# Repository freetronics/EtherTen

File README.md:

Freetronics EtherTen
====================
Copyright 2010-2013 Freetronics Pty Ltd  
Freetronics site:  www.freetronics.com  
Freetronics email: info@freetronics.com  

The EtherTen is a 100% Arduino Compatible Board, based on the Arduino
Uno reference design, but with improvements and updates for ease of use, cost
and getting started. It also includes on-board Ethernet with PoE (Power
-over-Ethernet) support.

Features:

 * LEDs visible on the edge
 * Micro-USB Connector
 * I2C MAC address ROM
 * Overlay guide where you need it (both top and bottom)
 * D13 pin works for everything
 * RX pin biased
 * Mounting holes, power and X3 pads
 * All connections in the same place

You can view more at our product page at:

  http://www.freetronics.com/etherten

This repository includes a handy copy of the schematic in PDF format.

INSTALLATION
------------
The design is saved as an EAGLE project. EAGLE PCB design software is
available from www.cadsoftusa.com free for non-commercial use. To use
this project download it and place the directory containing these files
into the "eagle" directory on your computer. Then open EAGLE and
navigate to Projects -> eagle -> EtherTen.

DISTRIBUTION
------------
The specific terms of distribution of this project are governed by the
license referenced below.

LICENSE
-------
This work is licensed under the
Creative Commons Attribution-Share Alike License.  
To view a copy of this license, visit

  http://creativecommons.org/licenses/by-sa/3.0/  
  http://creativecommons.org/licenses/by-sa/3.0/legalcode

or send a letter to

  Creative Commons  
  171 Second Street, Suite 300  
  San Francisco  
  California, 94105  
  USA

The "license" folder within this repository also contains copies of the
licences referenced above.

CREDITS
-------
The EtherTen was designed by Marc Alexander (marc@freetronics.com) and
Jonathan Oxer (jon@freetronics.com) based on previous work by the Arduino
team (www.arduino.cc/playground/Main/People) which includes:

 * Massimo Banzi
 * David Cuartielles
 * Tom Igoe
 * Gianluca Martino
 * David A. Mellis

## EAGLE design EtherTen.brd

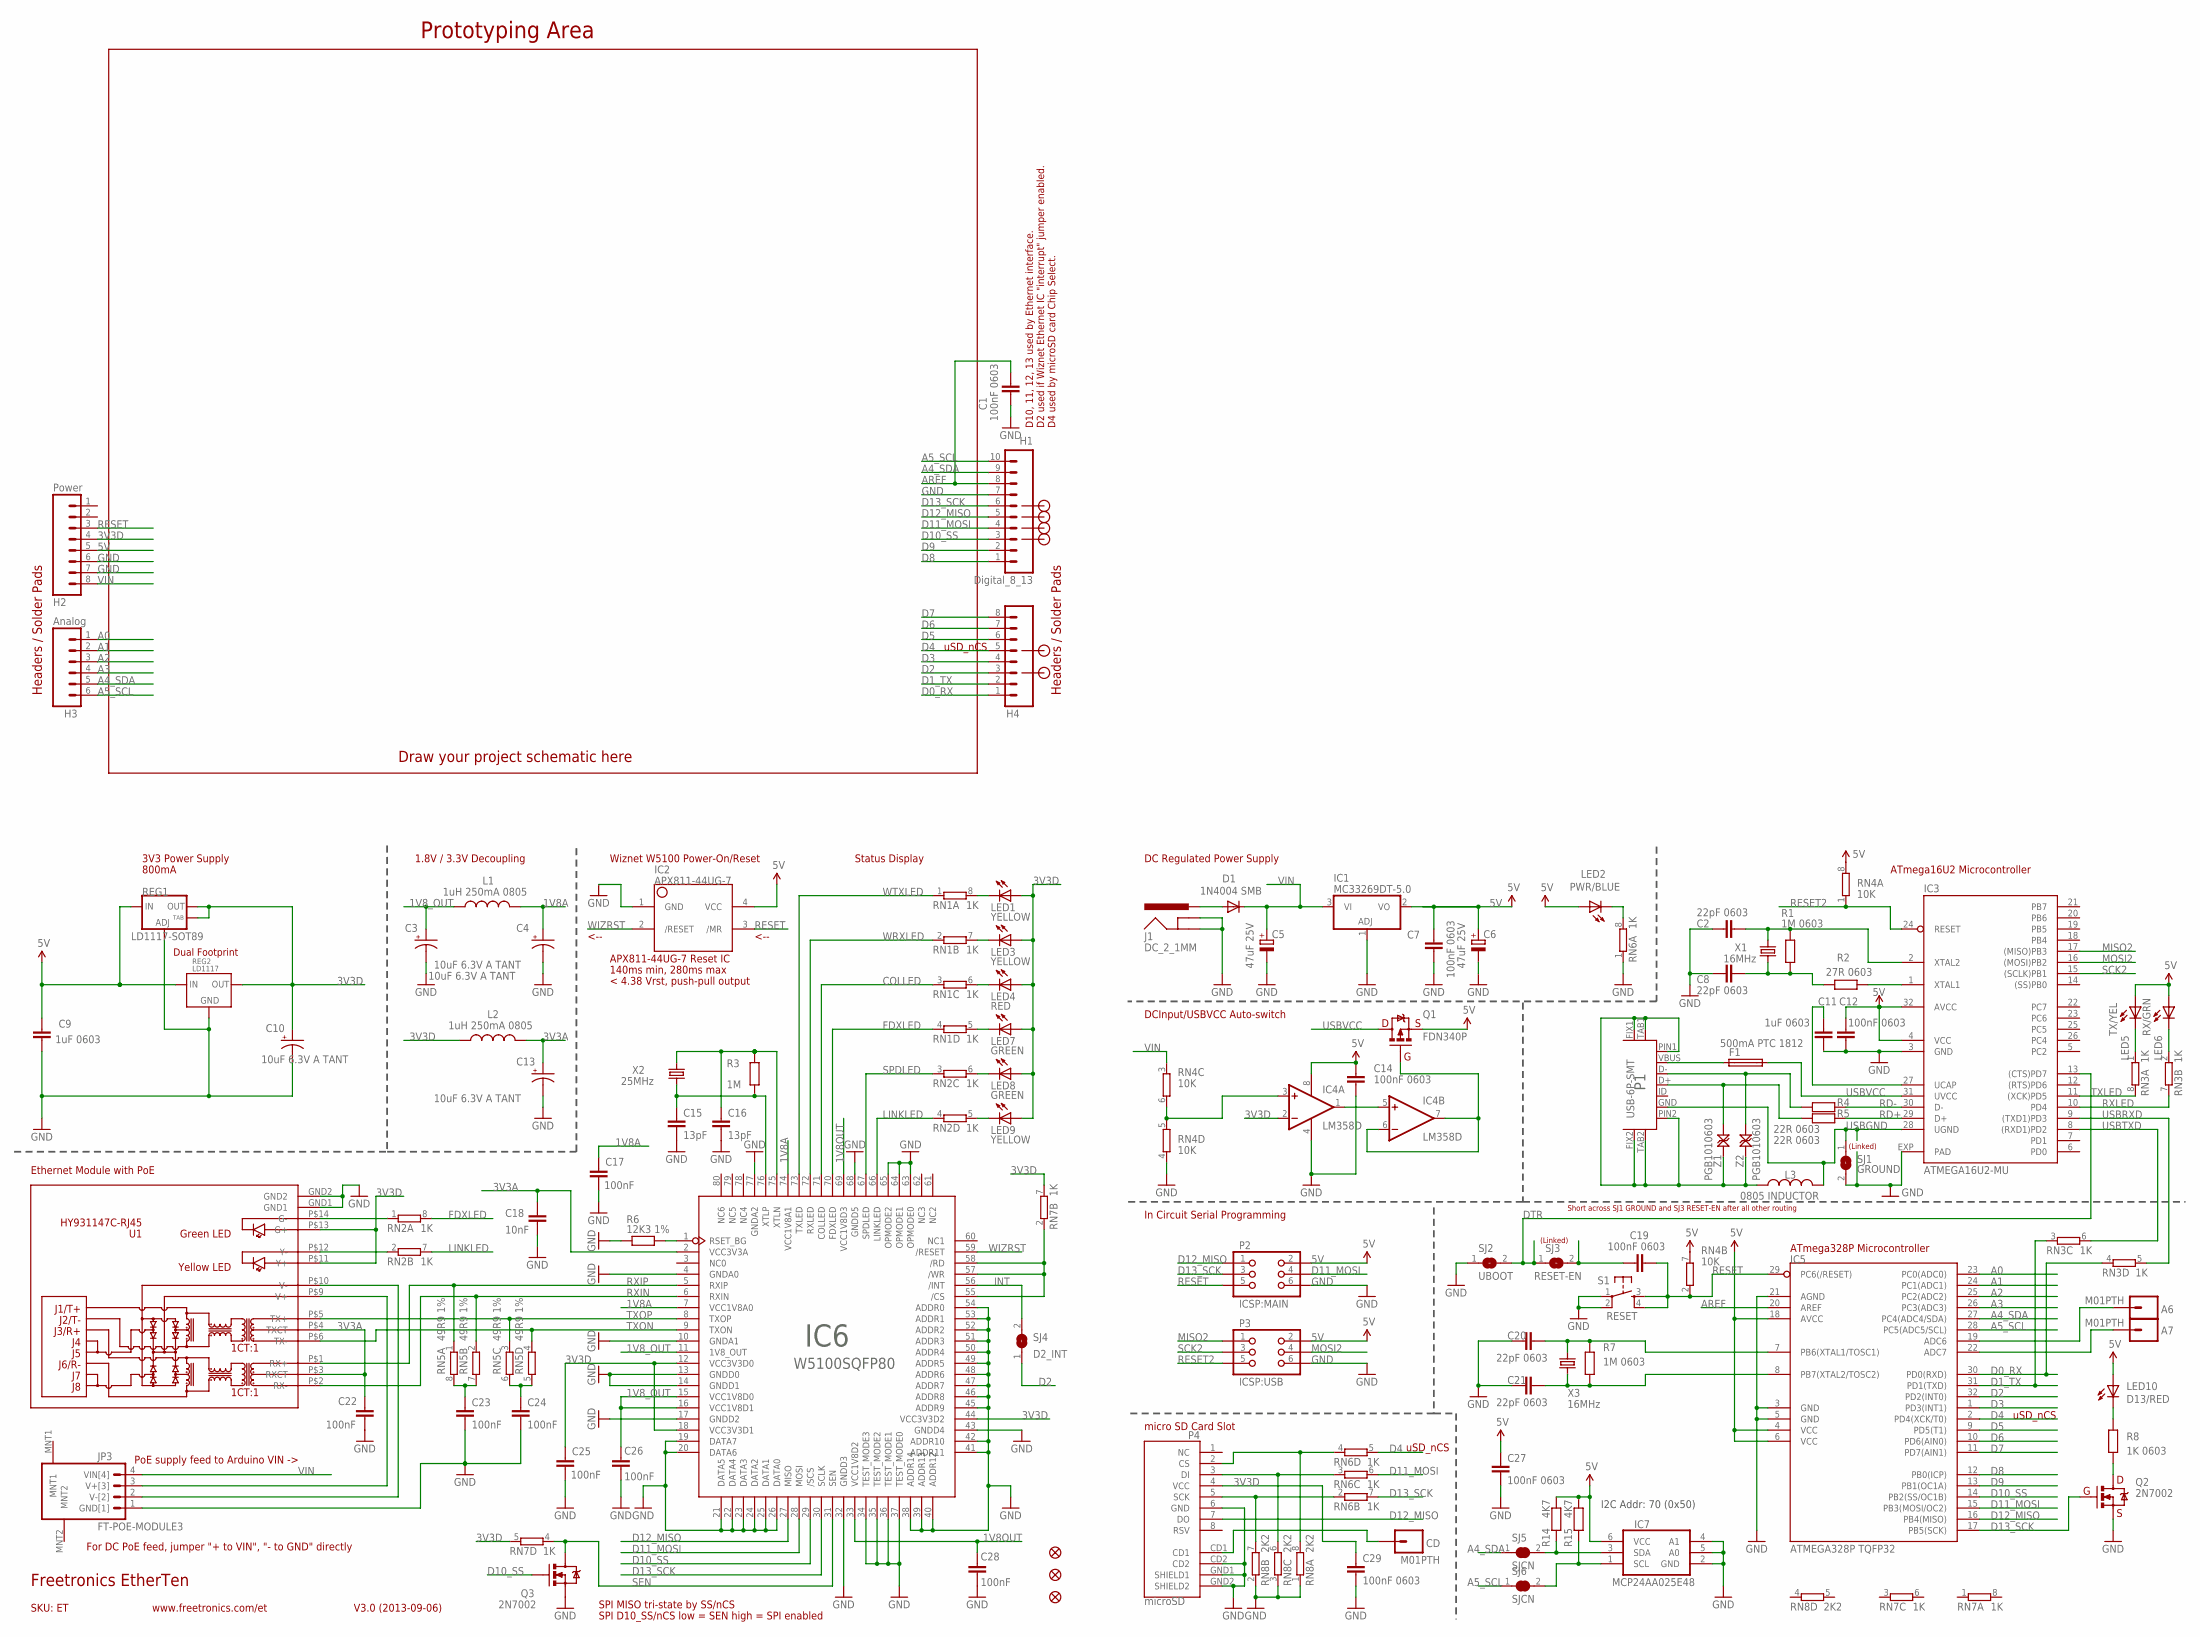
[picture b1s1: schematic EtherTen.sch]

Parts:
A6, A7: M01PTH; 1X01
C1, C7, C12, C14, C19, C27, C29: 100nF 0603; C0603
C2, C8, C20, C21: 22pF 0603; C0603
C3, C4, C10, C13: 10uF 6.3V A TANT; EIA3216
C5, C6: 47uF 25V; PANASONIC_D
C9, C11: 1uF 0603; C0603
C15, C16: 13pF; C0603
C17, C22, C23, C24, C25, C26, C28: 100nF; C0603
C18: 10nF; C0603
CD: M01PTH; 1X01
D1: 1N4004 SMB; SMA-DIODE
F1: 500mA PTC 1812; 1812
FID1, FID2, FID3: FIDUCIAL1X2.5; FIDUCIAL-1X2.5
H1: Digital_8_13; 1X10-S
H2: Power; 1X08-S
H3: Analog; 1X06-S
H4: Digital_0_7; 1X08-S
IC1: MC33269DT-5.0; DPACK
IC2: APX811-44UG-7; SOT143-R
IC3: ATMEGA16U2-MU; ATMEL_QFN32
IC4: LM358D; SO08
IC5: ATMEGA328P TQFP32; TQFP32-08
IC6: W5100SQFP80; SQFP80
IC7: MCP24AA025E48; SOT23-6
J1: DC_2_1MM; POWER_JACK_SLOTS
JP3: FT-POE-MODULE3; FT-POE-MODULE-NOLABEL
L1, L2: 1uH 250mA 0805; L2012C
L3: 0805 INDUCTOR; 0805-LARGE
LED1, LED3, LED9: YELLOW; LED-0603
LED2: PWR/BLUE; LED-0603
LED4: RED; LED-0603
LED5: TX/YEL; LED-0603
LED6: RX/GRN; LED-0603
LED7, LED8: GREEN; LED-0603
LED10: D13/RED; LED-0603
P1: USB-6P-SMT; USB-MICROB-MB05PMXX
P2: ICSP:MAIN; 2X03PTH
P3: ICSP:USB; 2X03PTH
P4: microSD; MICRO-SD-SOCKET-PP
Q1: FDN340P; SOT23
Q2, Q3: 2N7002; SOT23-3
R1, R7: 1M 0603; R0603
R2: 27R 0603; R0603
R3: 1M; R0603
R4, R5: 22R 0603; R0603
R6: 12K3 1%; R0603
R8: 1K 0603; R0603
R14, R15: 4K7; R0603
REG1: LD1117-SOT89; SOT89
REG2: LD1117; SOT-223
RN1, RN2, RN3, RN6, RN7: 1K; CAY16
RN4: 10K; CAY16
RN5: 49R9 1%; CAY16
RN8: 2K2; CAY16
S1: RESET; TACTILE_SMD-6MM
SJ1: GROUND; SJ
SJ2: UBOOT; SJ
SJ3: RESET-EN; SJ
SJ4: D2_INT; SJ
SJ5, SJ6: SJCN; SJC
U1: HY931147C-RJ45; HY931147C
X1, X3: 16MHz; HC49U-V
X2: 25MHz; HC49U-V
Z1, Z2: PGB1010603; TVS0603

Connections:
1V8A: C4.A (+), C17.1, IC6.7 (VCC1V8A0), IC6.74 (VCC1V8A1), L1.2
1V8OUT: C28.1, IC6.33 (VCC1V8D2), IC6.69 (VCC1V8D3)
1V8_OUT: C3.A (+), C26.1, IC6.11 (1V8_OUT), IC6.15 (VCC1V8D0), IC6.16 (VCC1V8D1), L1.1
3V3A: C13.A (+), C18.1, C22.1, IC6.2 (VCC3V3A), L2.2, U1.P$3 (RXCT), U1.P$4 (TXCT)
3V3D: C10.A (+), C25.1, C29.1, H2.4, IC4.2 (-IN), IC6.12 (VCC3V3D0), IC6.18 (VCC3V3D1), IC6.44 (VCC3V3D2), L2.1, LED1.A, LED3.A, LED4.A, LED7.A, LED8.A, LED9.A, P4.4 (VCC), REG1.2 (OUT), REG1.4 (OUT), REG2.2 (OUT), REG2.4 (OUT), RN7.5 (2), RN7.7 (2), U1.P$11 (Y+), U1.P$13 (G+)
5V: C6.+, C7.1, C9.1, C12.1, C14.1, C27.1, H2.5, IC1.2 (VO), IC2.4 (VCC), IC3.4 (VCC), IC3.32 (AVCC), IC4.8 (V+), IC5.4 (VCC), IC5.6 (VCC), IC5.18 (AVCC), IC7.6 (VCC), LED2.A, LED5.A, LED6.A, LED10.A, P2.2, P3.2, Q1.2 (S), R14.1, R15.1, REG1.3 (IN), REG2.3 (IN), RN4.7 (2), RN4.8 (2)
A0: H3.1, IC5.23 (PC0(ADC0))
A1: H3.2, IC5.24 (PC1(ADC1))
A2: H3.3, IC5.25 (PC2(ADC2))
A3: H3.4, IC5.26 (PC3(ADC3))
A4_SDA: H1.9, H3.5, IC5.27 (PC4(ADC4/SDA)), SJ5.1
A5_SCL: H1.10, H3.6, IC5.28 (PC5(ADC5/SCL)), SJ6.1
AREF: C1.1, H1.8, IC5.20 (AREF)
COLLED: IC6.71 (COLLED), RN1.3 (1)
D0_RX: H4.1, IC5.30 (PD0(RXD)), RN3.4 (1)
D1_TX: H4.2, IC5.31 (PD1(TXD)), RN3.3 (1)
D2: H4.3, IC5.32 (PD2(INT0)), SJ4.1
D3: H4.4, IC5.1 (PD3(INT1))
D4: H4.5, IC5.2 (PD4(XCK/T0)), RN6.5 (2)
D5: H4.6, IC5.9 (PD5(T1))
D6: H4.7, IC5.10 (PD6(AIN0))
D7: H4.8, IC5.11 (PD7(AIN1))
D8: H1.1, IC5.12 (PB0(ICP))
D9: H1.2, IC5.13 (PB1(OC1A))
D10_SS: H1.3, IC5.14 (PB2(SS/OC1B)), IC6.29 (/SCS), Q3.1 (G)
D11_MOSI: H1.4, IC5.15 (PB3(MOSI/OC2)), IC6.28 (MOSI), P2.4, RN6.6 (2)
D12_MISO: H1.5, IC5.16 (PB4(MISO)), IC6.27 (MISO), P2.1, P4.7 (DO)
D13_SCK: H1.6, IC5.17 (PB5(SCK)), IC6.30 (SCLK), P2.3, Q2.1 (G), RN6.7 (2)
DTR: IC3.13 ((CTS)PD7), SJ2.2, SJ3.1
FDXLED: IC6.70 (FDXLED), RN1.4 (1), RN2.8 (2)
GND: C1.2, C2.1, C3.C (-), C4.C (-), C5.-, C6.-, C7.2, C8.1, C9.2, C10.C (-), C11.2, C12.2, C13.C (-), C14.2, C15.2, C16.2, C17.2, C18.2, C20.1, C21.1, C22.2, C23.2, C24.2, C25.2, C26.2, C27.2, C28.2, C29.2, H1.7, H2.6, H2.7, IC1.1 (ADJ), IC2.1 (GND), IC3.3 (GND), IC3.EXP (PAD), IC4.4 (V-), IC5.3 (GND), IC5.5 (GND), IC5.21 (AGND), IC6.4 (GNDA0), IC6.10 (GNDA1), IC6.13 (GNDD0), IC6.14 (GNDD1), IC6.17 (GNDD2), IC6.19 (DATA7), IC6.20 (DATA6), IC6.21 (DATA5), IC6.22 (DATA4), IC6.23 (DATA3), IC6.24 (DATA2), IC6.25 (DATA1), IC6.26 (DATA0), IC6.32 (GNDD3), IC6.34 (TEST_MODE3), IC6.35 (TEST_MODE2), IC6.36 (TEST_MODE1), IC6.37 (TEST_MODE0), IC6.38 (ADDR14), IC6.39 (ADDR13), IC6.40 (ADDR12), IC6.41 (ADDR11), IC6.42 (ADDR10), IC6.43 (GNDD4), IC6.45 (ADDR9), IC6.46 (ADDR8), IC6.47 (ADDR7), IC6.48 (ADDR6), IC6.49 (ADDR5), IC6.50 (ADDR4), IC6.51 (ADDR3), IC6.52 (ADDR2), IC6.53 (ADDR1), IC6.54 (ADDR0), IC6.63 (OPMODE0), IC6.64 (OPMODE1), IC6.65 (OPMODE2), IC6.68 (GNDD5), IC6.77 (GNDA2), IC7.2 (GND), IC7.4 (A1), IC7.5 (A0), J1.GND, J1.GNDBREAK, JP3.1 (GND[1]), P2.6, P3.6, P4.6 (GND), P4.CD2, P4.GND1 (SHIELD1), P4.GND2 (SHIELD2), Q2.2 (S), Q3.2 (S), R6.1, REG1.1 (ADJ), REG2.1 (GND), RN4.4 (1), RN6.1, RN8.1, RN8.2 (1), RN8.3 (1), S1.1, S1.2, SJ1.2, SJ2.1, U1.GND1, U1.GND2
INT: IC6.56 (/INT), SJ4.2
LINKLED: IC6.66 (LINKLED), RN2.4 (1), RN2.7 (2)
MISO2: IC3.17 ((MISO)PB3), P3.1
MOSI2: IC3.16 ((MOSI)PB2), P3.4
unnamed: C24.1, RN5.5 (2), RN5.6 (2)
unnamed: C20.2, IC5.7 (PB6(XTAL1/TOSC1)), R7.2, X3.2
unnamed: C19.1, SJ3.2
unnamed: LED10.C, R8.2
unnamed: IC7.1 (SCL), R15.2, SJ6.2
unnamed: Q2.3 (D), R8.1
unnamed: C21.2, IC5.8 (PB7(XTAL2/TOSC2)), R7.1, X3.1
unnamed: IC3.1 (XTAL1), R2.1
unnamed: L3.1, P1.FIX1, P1.FIX2, P1.PIN1, P1.PIN2, P1.TAB1, P1.TAB2, Z1.2, Z2.2
unnamed: LED6.C, RN3.2 (1)
unnamed: IC4.3 (+IN), RN4.5 (2), RN4.6 (2)
unnamed: LED5.C, RN3.1
unnamed: LED2.C, RN6.8 (2)
unnamed: P1.D+, R5.2, Z1.1
unnamed: P1.D-, R4.2, Z2.1
unnamed: IC4.6 (-IN), IC4.7 (OUT), Q1.1 (G)
unnamed: IC4.1 (OUT), IC4.5 (+IN)
unnamed: P4.2 (CS), RN6.4 (1), RN8.8 (2)
unnamed: A7.1, IC5.22 (ADC7)
unnamed: A6.1, IC5.19 (ADC6)
unnamed: CD.1, P4.CD1
unnamed: P4.5 (SCK), RN6.2 (1), RN8.7 (2)
unnamed: P4.3 (DI), RN6.3 (1), RN8.6 (2)
unnamed: LED8.C, RN2.6 (2)
unnamed: IC6.55 (/CS), IC6.57 (/WR), IC6.58 (/RD), RN7.2 (1)
unnamed: LED9.C, RN2.5 (2)
unnamed: IC7.3 (SDA), R14.2, SJ5.2
unnamed: D1.A, J1.PWR
unnamed: RN2.1, U1.P$14 (G-)
unnamed: JP3.3 (V+[3]), U1.P$9 (V+)
unnamed: JP3.2 (V-[2]), U1.P$10 (V-)
unnamed: C2.2, IC3.2 (XTAL2), R1.2, X1.2
unnamed: C8.2, R1.1, R2.2, X1.1
unnamed: F1.1, P1.VBUS
unnamed: C11.1, IC3.27 (UCAP)
unnamed: C23.1, RN5.7 (2), RN5.8 (2)
unnamed: IC6.1 (RSET_BG), R6.2
unnamed: LED7.C, RN1.5 (2)
unnamed: LED4.C, RN1.6 (2)
unnamed: LED3.C, RN1.7 (2)
unnamed: LED1.C, RN1.8 (2)
unnamed: RN2.2 (1), U1.P$12 (Y-)
RD+: IC3.29 (D+), R5.1
RD-: IC3.30 (D-), R4.1
RESET: C19.2, H2.3, IC2.3 (/MR), IC5.29 (PC6(/RESET)), P2.5, RN4.2 (1), S1.3, S1.4
RESET2: IC3.24 (RESET), P3.5, RN4.1
RXIN: IC6.6 (RXIN), RN5.2 (1), U1.P$2 (RX-)
RXIP: IC6.5 (RXIP), RN5.1, U1.P$1 (RX+)
RXLED: IC3.10 (PD4), RN3.7 (2)
SCK2: IC3.15 ((SCLK)PB1), P3.3
SEN: IC6.31 (SEN), Q3.3 (D), RN7.4 (1)
SPDLED: IC6.67 (SPDLED), RN2.3 (1)
TXLED: IC3.11 ((XCK)PD5), RN3.8 (2)
TXON: IC6.9 (TXON), RN5.4 (1), U1.P$6 (TX-)
TXOP: IC6.8 (TXOP), RN5.3 (1), U1.P$5 (TX+)
USBGND: IC3.28 (UGND), L3.2, P1.GND, SJ1.1
USBRXD: IC3.9 ((TXD1)PD3), RN3.5 (2)
USBTXD: IC3.8 ((RXD1)PD2), RN3.6 (2)
USBVCC: F1.2, IC3.31 (UVCC), Q1.3 (D)
VIN: C5.+, D1.C, H2.8, IC1.3 (VI), JP3.4 (VIN[4]), RN4.3 (1)
WIZRST: IC2.2 (/RESET), IC6.59 (/RESET)
WRXLED: IC6.72 (RXLED), RN1.2 (1)
WTXLED: IC6.73 (TXLED), RN1.1
XTLN: C16.1, IC6.75 (XTLN), R3.2, X2.2
XTLP: C15.1, IC6.76 (XTLP), R3.1, X2.1

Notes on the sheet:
Prototyping Area
SKU: ET
3V3 Power Supply
Status Display
Headers / Solder Pads
Dual Footprint
1.8V / 3.3V Decoupling
Draw your project schematic here
D10, 11, 12, 13 used by Ethernet interface.
D2 used if Wiznet Ethernet IC "interrupt" jumper enabled.
PoE supply feed to Arduino VIN ->
SPI MISO tri-state by SS/nCS
SPI D10_SS/nCS low = SEN high = SPI enabled
For DC PoE feed, jumper "+ to VIN", "- to GND" directly
DC Regulated Power Supply
ATmega328P Microcontroller
APX811-44UG-7 Reset IC
140ms min, 280ms max
ATmega16U2 Microcontroller
DCInput/USBVCC Auto-switch
Wiznet W5100 Power-On/Reset
uSD_nCS
800mA
In Circuit Serial Programming
micro SD Card Slot
Freetronics EtherTen
V3.0 (2013-09-06)
www.freetronics.com/et
Ethernet Module with PoE
< 4.38 Vrst, push-pull output
<--
D4 used by microSD card Chip Select.
(Linked)
Short across SJ1 GROUND and SJ3 RESET-EN after all other routing
I2C Addr: 70 (0x50)

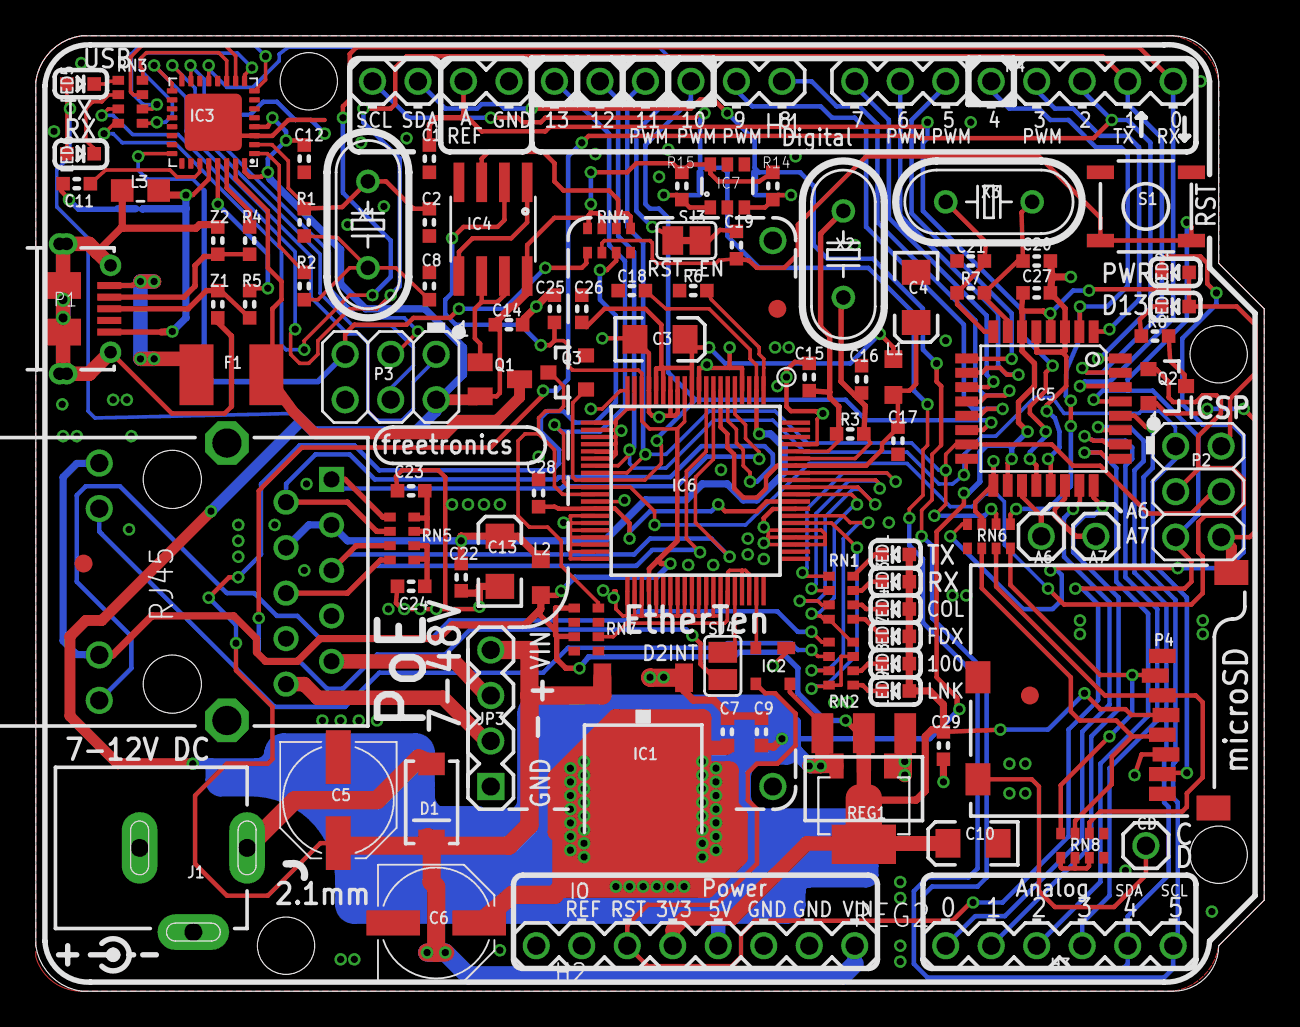
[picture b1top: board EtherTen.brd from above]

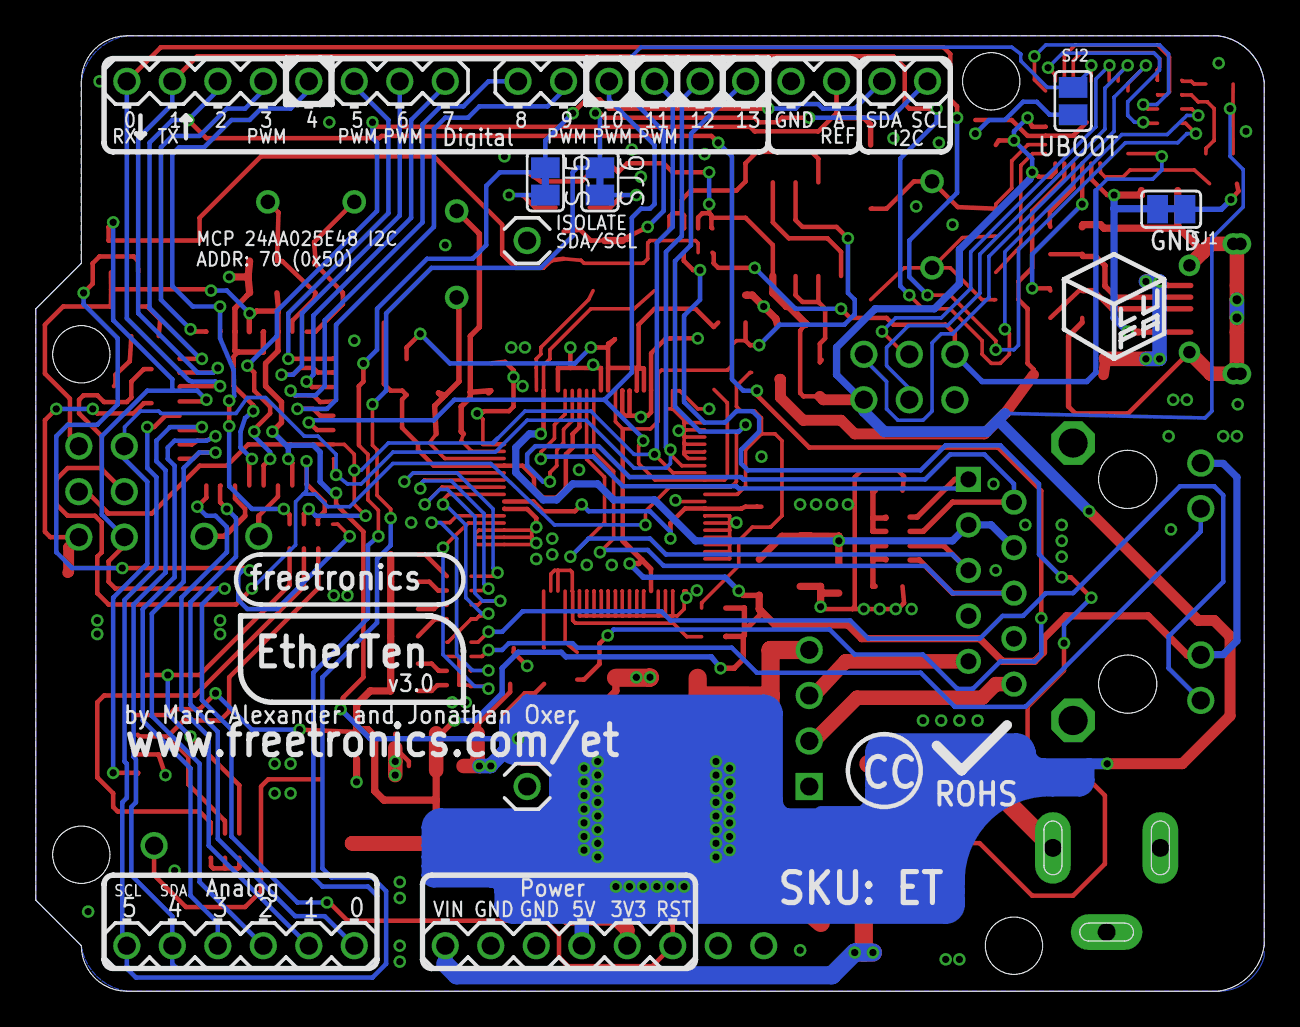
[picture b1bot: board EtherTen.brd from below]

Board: 2 copper layers, 68.6 x 53.3 mm, 103 parts (4 on the bottom side), 100 nets.

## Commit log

2010-06-27 Added README
2010-06-27 Initial creation of schematic and PCB based on TwentyTen
2010-06-27 Added Ethernet section to schematic
2010-06-27 Replaced fiducial markers
2010-07-08 Latest merged ES and TT
2010-08-11 Recreated project by merging TwentyTen and Ethernet Shield
2010-08-13 Removed parts duplicated between TT and ES schematics, and updated schematic layout
2010-08-13 Start of shoving things into place
2010-08-24 Replaced AVR package with TQFP32
2010-08-24 Moved PoE header back to left of board and added sub-board mounting holes
2010-09-19 Moved parts closer to board
2010-09-20 Removed header breakouts and switched to TT style header labels
2010-09-23 New locations, ripup ready for rework
2010-11-10 Squeezing and rearranging parts, new notes
2011-02-19 New sch passes ERC
2011-02-21 Lots of squeezing
2011-02-23 All squeezed into pcb outline
2011-03-10 Last fiddly routes
2011-03-16 Squeezy tracks
2011-03-17 Zero airwires :)
2011-03-17 Last DRC checks
2011-03-17 TL Polygon orphans on, more notes
2011-03-17 v1_0 production release
2011-05-08 v1.1 - Pin usage on silkscreen artwork, more heatsink vias and area, microSD CD pad revision. Parts not moved.
2011-05-08 v1.1 PDF sch renamed to suit
2012-07-04 Renamed project files for R3 version
2012-07-04 Initial changes to R3
2012-07-05 Beginning of conversion to R3
2012-07-06 Routing for R3 revision
2012-07-06 More routing for R3
2012-07-06 Improved I2C and ICSP markings; ERC and DRC for release
2012-07-06 Improved designator visibility
2012-07-07 Production release R3 v2.0 files
2013-09-06 Added I2C MAC ROM in preparation for v3.0
2013-09-06 Updated dates and features in README
2013-09-06 Added v3.0 schematic PDF
2019-07-01 Replaced most parts using SuperHouse library to add 3D models
2019-07-07 Replaced more parts using SuperHouse libraries
